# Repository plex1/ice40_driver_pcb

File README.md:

# iCE40 Signal Driver
Extension module for iCE40HX1K-EVB or iCE40HX8K-EVB.

Contains 
- variable delay IC and
- signal drivers and receivers for 50 Ohms UMCC cables.

License information should be found in LICENSE.txt

## Rendered PCB

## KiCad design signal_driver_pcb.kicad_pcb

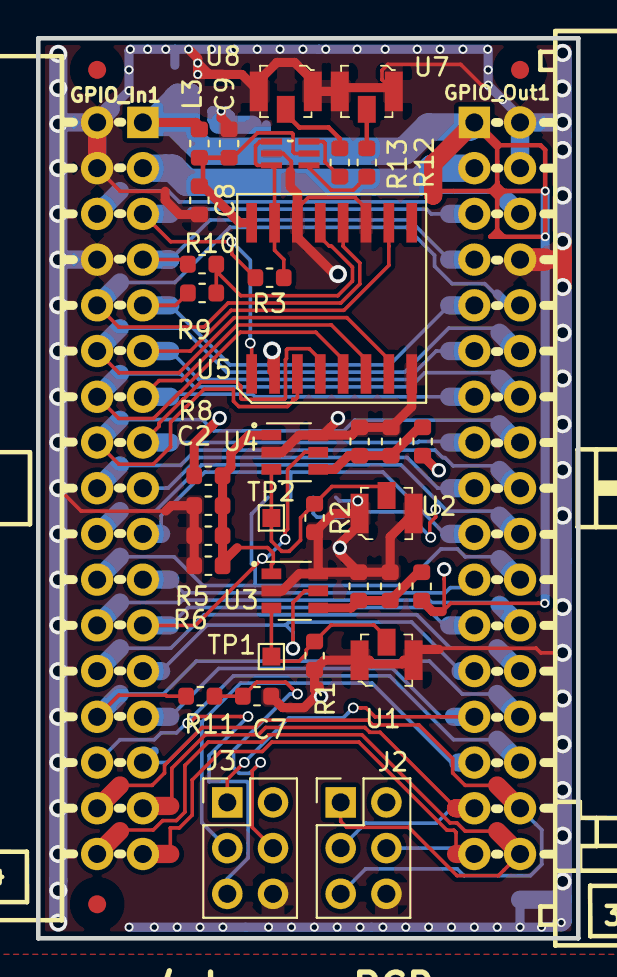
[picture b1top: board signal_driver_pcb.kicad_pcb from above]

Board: 4 copper layers, 30.0 x 50.0 mm, 37 parts (1 on the bottom side), 45 nets.

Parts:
C2, C5, C6, C8: 2.2uF; C_0603_1608Metric
C3, C4, C9: 100nF; C_0603_1608Metric
C7: 100pF; C_0603_1608Metric
GPIO_In1: IDC34R; IDC34R_PCB
GPIO_Out1: BH34R
J1: Conn_01x04; Molex_PicoBlade_53261-0471_1x04-1MP_P1.25mm_Horizontal
J2, J3: Conn_02x03_Odd_Even; PinHeader_2x03_P2.54mm_Vertical
L1, L2, L3: bead; L_0603_1608Metric
R1, R2: 50R; R_0603_1608Metric
R3, R9, R10: 0R; R_0603_1608Metric
R5, R6, R8, R11: 2.2k; R_0603_1608Metric
R12, R13: 22R; R_0603_1608Metric
TP1, TP2: TestPoint; TestPoint_Pad_1.0x1.0mm
U1, U2, U7, U8: UMCC_50Ohm; Molex_734120114_UMC_RF_CONN_Vertical
U3, U4: TLV3501; SOT-23-6
U5: DS1023; SOIC-16_300mil
U6: NC7WZ16; SOT65P210X110-6N

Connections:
+3V3: GPIO_In1.3, GPIO_Out1.3
+5V: GPIO_In1.1, GPIO_Out1.1, J2.2, J3.2, L1.1, L2.1, L3.2, R8.1, U5.2
/EXTCLK: GPIO_In1.6, GPIO_Out1.6
/GPIO_Pin<17>: GPIO_In1.17, GPIO_Out1.17
/GPIO_Pin<18>: GPIO_In1.18, GPIO_Out1.18
/GPIO_Pin<21>: GPIO_In1.21, GPIO_Out1.21
/GPIO_Pin<24>: GPIO_In1.24, GPIO_Out1.24
/GPIO_Pin<26>: GPIO_In1.26, GPIO_Out1.26
/GPIO_Pin<29>: GPIO_In1.29, GPIO_Out1.29, J3.3
/GPIO_Pin<30>: GPIO_In1.30, GPIO_Out1.30, J3.5
/TCK: GPIO_In1.31, GPIO_Out1.31, J2.3
/TDI: GPIO_In1.33, GPIO_Out1.33, J2.4
/TDO: GPIO_In1.34, GPIO_Out1.34, J2.1
/TMS: GPIO_In1.32, GPIO_Out1.32, J2.5
/TrigsIn0: GPIO_In1.23, GPIO_Out1.23, U4.5
/TrigsIn0_con: R2.1, TP2.1, U2.2, U4.3
/TrigsIn1: GPIO_In1.25, GPIO_Out1.25, U3.5
/TrigsIn1_con: R1.1, TP1.1, U1.2, U3.3
/TrigsOut: GPIO_In1.5, GPIO_Out1.5, R3.2, U5.1
/TrigsOut_delay: R3.1, U5.15, U6.1, U6.3
/UartRx: GPIO_In1.28, GPIO_Out1.28, R11.2
/UartRx_filt: C7.1, J3.4, R11.1
/UartTx: GPIO_In1.27, GPIO_Out1.27, J3.1
/delay0: GPIO_In1.16, GPIO_Out1.16, U5.3
/delay1: GPIO_In1.15, GPIO_Out1.15, U5.4
/delay2: GPIO_In1.14, GPIO_Out1.14, U5.5
/delay3: GPIO_In1.13, GPIO_Out1.13, U5.6
/delay4: GPIO_In1.12, GPIO_Out1.12, U5.7
/delay5: GPIO_In1.11, GPIO_Out1.11, U5.10
/delay6: GPIO_In1.10, GPIO_Out1.10, U5.12
/delay7: GPIO_In1.9, GPIO_Out1.9, R9.2
/delay7_alt: GPIO_In1.7, GPIO_Out1.7, R10.2
/delay7_sel: R9.1, R10.1, U5.13
/lockin_1: GPIO_In1.19, GPIO_Out1.19, J1.3
/lockin_2: GPIO_In1.20, GPIO_Out1.20, J1.2
/supply_buffer: C8.1, C9.1, L3.1, U5.16, U6.5
/sync1: GPIO_In1.22, GPIO_Out1.22, J1.4
/th: C2.1, R5.1, R6.1, R8.2, U3.1, U4.1
GND: C2.2, C3.2, C4.2, C5.2, C6.2, C7.2, C8.2, C9.2, GPIO_In1.2, GPIO_In1.4, GPIO_In1.8, GPIO_Out1.2, GPIO_Out1.4, GPIO_Out1.8, J1.1, J2.6, J3.6, R1.2, R2.2, R5.2, R6.2, U1.1, U1.3, U2.1, U2.3, U3.2, U3.6, U4.2, U4.6, U5.8, U5.11, U5.14, U6.2, U7.1, U7.3, U8.1, U8.3
unnamed: C3.1, C5.1, L1.2, U3.4
unnamed: C4.1, C6.1, L2.2, U4.4
unnamed: R12.1, U7.2
unnamed: R12.2, U6.4
unnamed: R13.1, U8.2
unnamed: R13.2, U6.6

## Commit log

2019-11-19 Initial version
2024-08-07 committed previously uncommitted changes
2024-08-07 added additional files (schematic, etc)
2024-08-07 added rendered image

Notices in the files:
signal_driver_pcb.kicad_pcb:
(C) 2019
